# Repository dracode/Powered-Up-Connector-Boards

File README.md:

# Powered-Up-Connector-Boards
This repository contains the circuit board layouts I created to use the Powered Up (aka WeDo 2.0) cables and sockets that I found on AliExpress.

I used these connectors, found on a shop at <A HREF="https://www.aliexpress.com/item/33057514281.html">AliExpress</A>, to make my boards.
<TABLE>
  <TR><TD><B>Female</B></TD><TD><B>Male</B></TD></TR>
  <TR><TD><IMG SRC="./wedo_2.0.pretty/Female%20Connector.png"></TD><TD><IMG SRC="./wedo_2.0.pretty/Male%20Connector.png"></TR>
</TABLE>
The male cable will work with a standard 1.27mm pitch pin header.  I created a KiCad part/footprint for the female connector in the "wedo_2.0.lib" and "wedo_2.0.pretty" library.<P>
The female connector has two locating pins on the bottom that will snap in place into the board.  The "neck" on these pins is only approximately 1mm long, so ensure your board is thinner than that if you want the connector to snap into place properly.  I used 0.8mm thickness PCB from <A HREF="https://oshpark.com">OSHPark.com</A> and it worked well.<P>
<P>
Boards I have designed so far:<P>
<TABLE>
<TR><TH>OSHPark Link</TH><TH>Render</TH></TR>
<TR><TD><A HREF="https://oshpark.com/shared_projects/C05HhJQx">Powered Up Extender</A></TD><TD><IMG SRC="Powered%20Up%20Extender/Extender%20Board%20Render.png" /></TD></TR>
<TR><TD><A HREF="https://oshpark.com/shared_projects/9tZOPjXH">Powered Up Extender + 0.1&quot; Pin Headers</A></TD><TD><IMG SRC="Powered%20Up%20Sniffer/PU%20Sniffer%20Board%20Render.png" /></TD></TR>
<TR><TD><A HREF="https://oshpark.com/shared_projects/ryhlzi0H">Powered Up Train Motor Splitter</A></TD><TD><IMG SRC="Powered%20Up%20Splitter/Splitter%20Board%20Render.png" /></TD></TR>
<TR><TD><A HREF="https://oshpark.com/shared_projects/m9qytbsl">Powered Up to Power Functions Adapter</A></TD><TD><IMG SRC="Powered%20Up%20to%20Power%20Functions/PU%20to%20PF%20Board%20Render.png" /></TD></TR>
</TABLE>

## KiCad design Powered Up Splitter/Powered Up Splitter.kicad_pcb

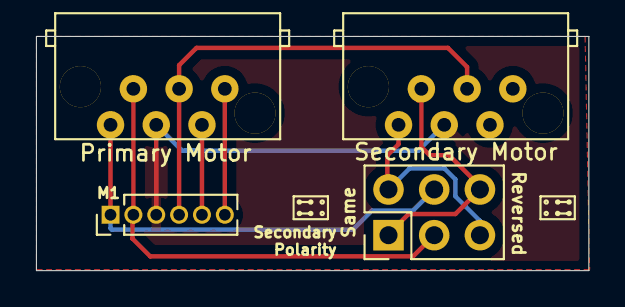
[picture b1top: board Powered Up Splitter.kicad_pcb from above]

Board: 2 copper layers, 30.7 x 13.0 mm, 4 parts (0 on the bottom side), 8 nets.

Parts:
J1, J2: FemaleConnector; WeDo 2.0 Female Socket
J3: Conn_01x06; PinHeader_1x06_P1.27mm_Vertical
J4: Conn_02x03_Row_Letter_First; PinHeader_2x03_P2.54mm_Vertical

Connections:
/3V3: J1.4, J2.4, J3.4
/GND: J1.3, J2.3, J3.3
/M1: J1.1, J3.1, J4.4
/M2: J1.2, J3.2, J4.3
unnamed: J1.5, J3.5
unnamed: J1.6, J3.6
unnamed: J2.1, J4.2, J4.5
unnamed: J2.2, J4.1, J4.6

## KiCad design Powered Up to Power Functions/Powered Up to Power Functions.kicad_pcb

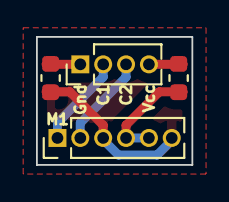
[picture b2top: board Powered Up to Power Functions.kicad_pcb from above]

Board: 2 copper layers, 8.6 x 7.1 mm, 4 parts (0 on the bottom side), 6 nets.

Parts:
J1: Conn_01x04; PinHeader_1x04_P1.27mm_Vertical
J3: Conn_01x06; PinHeader_1x06_P1.27mm_Vertical
R1, R2: R_Small_US; R_0603_1608Metric

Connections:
/3V3: J3.4, J3.5, R1.2
/GND: J3.3, J3.6, R2.2
/M1: J1.2, J3.1
/M2: J1.3, J3.2
unnamed: J1.1, R2.1
unnamed: J1.4, R1.1

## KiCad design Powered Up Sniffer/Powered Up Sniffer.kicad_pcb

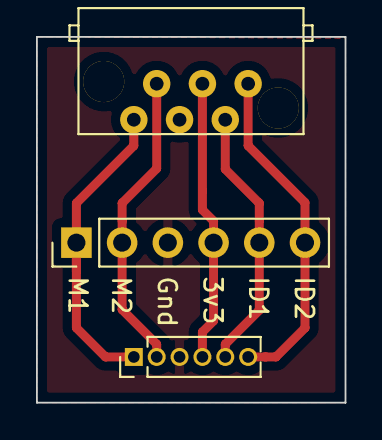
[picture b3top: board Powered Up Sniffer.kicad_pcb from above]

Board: 2 copper layers, 17.1 x 20.3 mm, 3 parts (0 on the bottom side), 6 nets.

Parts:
J1: FemaleConnector; WeDo 2.0 Female Socket
J2: Conn_01x06; PinHeader_1x06_P2.54mm_Vertical
J3: Conn_01x06; PinHeader_1x06_P1.27mm_Vertical

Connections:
/3V3: J1.4, J2.4, J3.4
/GND: J1.3, J2.3, J3.3
/M1: J1.1, J2.1, J3.1
/M2: J1.2, J2.2, J3.2
unnamed: J1.5, J2.5, J3.5
unnamed: J1.6, J2.6, J3.6
